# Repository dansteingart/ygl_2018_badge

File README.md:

## Overview

This is the sensor and code layout for the YGL 2018 Badge. 

The badge measures
- Ambient Temperature (via a DHT22 and a MLX90614)
- Focussed Temperature (via a MLX90614)
- Ambient Humidity (via a DHT22)

The badge also allows the wearer to indicate comfort level
- Red (hot)
- Blue (cold)
- Green (comfortable)

The badge attempts to connect to preprogammed wifi SSID's, and if it is connect it reports the ambient conditions once a minute and the user comfort on signaling.

## Board Schematics

The board can be edited in [Eagle](https://www.autodesk.com/products/eagle/free-download) 

## Code

The code for this is meant to be uploaded through the [build.particle.io](https://build.particle.io), but can also be compiled and sent remotely.

## How To Measure Things
This [document](https://docs.google.com/document/d/e/2PACX-1vTs8eymRHai5XaTd2wvhhjKwmNey0X5QBFbXBKoaI53rYneKwUvtwl-gOKRnENuz1WqiknrLIXWhSsD/pub)([PDF](https://docs.google.com/document/d/11KgSaUlBZMfQc9rQ66gh0Wr3Of6fnvB99Y8Q6VOIqZM/export?format=pdf)) describes how and why this all works, and what we're trying to do.

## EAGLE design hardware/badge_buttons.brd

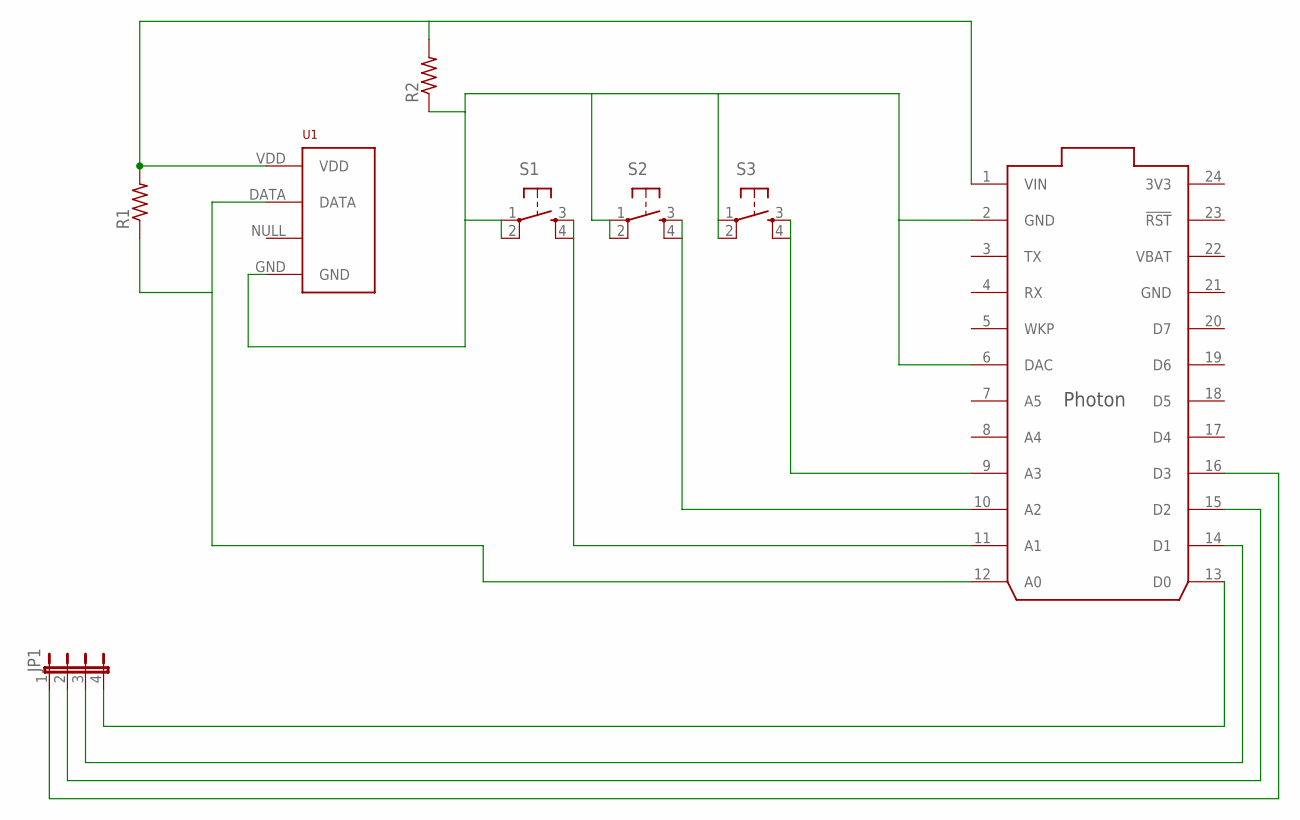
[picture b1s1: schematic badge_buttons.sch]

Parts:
JP1: JP4E; JP4
R1, R2: R-US_0204/7; 0204/7
S1, S2, S3: TAC_SWITCHPTH; TACTILE-PTH
U1: RHT03_DHT-22_AM2302; RHT03_DHT-22
U$1: PHOTON_WITH_HEADERS; PHOTON

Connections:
3V3: U$1.24 (3V3)
GND: U$1.21 (GND)
unnamed: S3.3, S3.4, U$1.9 (A3)
unnamed: S2.3, S2.4, U$1.10 (A2)
unnamed: S1.3, S1.4, U$1.11 (A1)
unnamed: R2.1, S1.1, S1.2, S2.1, S2.2, S3.1, S3.2, U1.GND, U$1.2 (GND), U$1.6 (DAC)
unnamed: R1.2, R2.2, U1.VDD, U$1.1 (VIN)
unnamed: R1.1, U1.DATA, U$1.12 (A0)
unnamed: JP1.4, U$1.13 (D0)
unnamed: JP1.3, U$1.14 (D1)
unnamed: JP1.2, U$1.15 (D2)
unnamed: JP1.1, U$1.16 (D3)
VBAT: U$1.22 (VBAT)

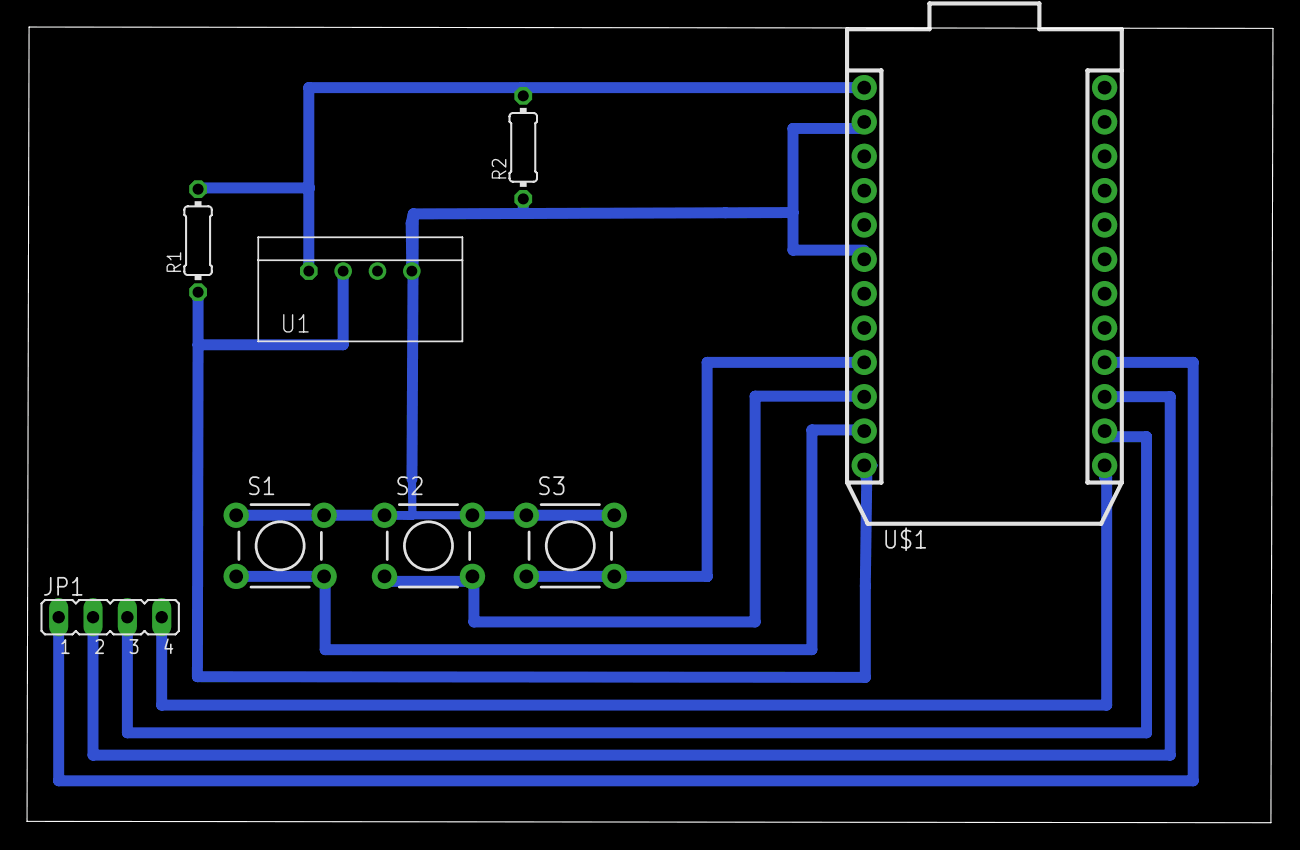
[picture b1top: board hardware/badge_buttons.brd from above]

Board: 2 copper layers, 92.2 x 58.9 mm, 8 parts (0 on the bottom side), 10 nets.

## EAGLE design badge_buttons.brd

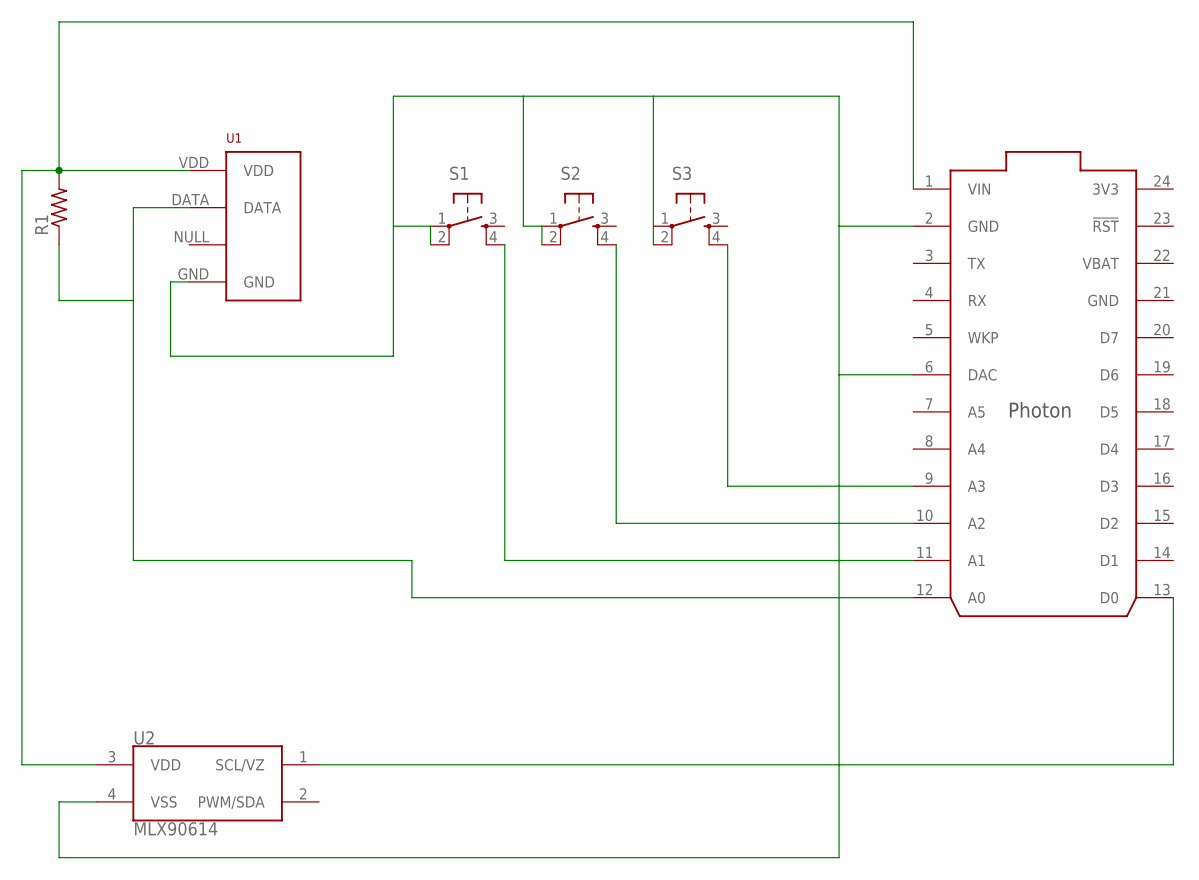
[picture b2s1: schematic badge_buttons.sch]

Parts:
R1: R-US_0204/7; 0204/7
S1, S2, S3: TAC_SWITCHPTH; TACTILE-PTH
U1: RHT03_DHT-22_AM2302; RHT03_DHT-22
U2: MLX90614; TO-39
U$1: PHOTON_WITH_HEADERS; PHOTON

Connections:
3V3: U$1.24 (3V3)
GND: U$1.21 (GND)
unnamed: S3.4, U$1.9 (A3)
unnamed: S2.4, U$1.10 (A2)
unnamed: S1.4, U$1.11 (A1)
unnamed: S1.1, S1.2, S2.1, S2.2, S3.1, S3.2, U1.GND, U2.4 (VSS), U$1.2 (GND), U$1.6 (DAC)
unnamed: R1.2, U1.VDD, U2.3 (VDD), U$1.1 (VIN)
unnamed: R1.1, U1.DATA, U$1.12 (A0)
unnamed: U2.1 (SCL/VZ), U$1.13 (D0)
VBAT: U$1.22 (VBAT)

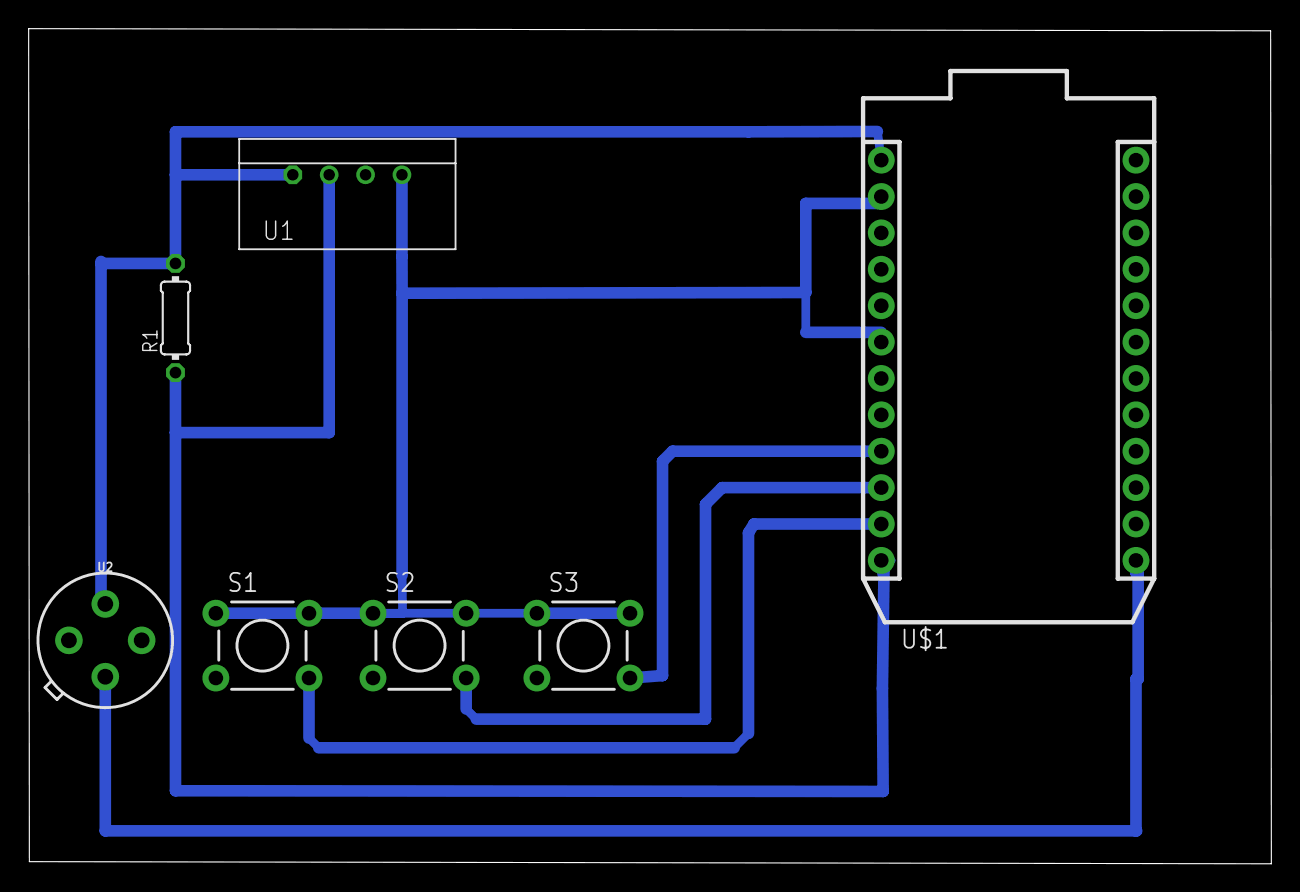
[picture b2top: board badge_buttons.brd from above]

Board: 2 copper layers, 86.8 x 58.3 mm, 7 parts (0 on the bottom side), 7 nets.

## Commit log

2018-05-30 first files
2018-06-07 clean up lines, add sensor loop
2018-06-07 fatten traces
2018-06-07 added README
2018-06-07 Rename README to README.md
2018-06-07 MLX succesfully added to code
2018-06-07 refactor directory/finish wiring
2018-06-07 started ToO
2018-06-07 more ToO
2018-06-08 add powershield SOC/Cell Potential
2018-06-08 fixed analogread bug
2018-06-08 code cleanup
2018-06-08 commented the ino
2018-06-08 Too much ToO
2018-06-08 sensible button order
2018-06-28 last add
2018-06-28 pusher T
2018-06-28 Wingoneer Change
2018-06-28 fattened pads
2018-06-28 othermill layout for 1x2 cut
2018-06-29 power hogging
2018-07-13 improve speed, triggers
2018-07-15 fix comfort send
2018-10-12 cleanup

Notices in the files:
parts and their libraries:
SparkFun-Retired: Licensing: Creative Commons ShareAlike 4.0 International - https://creativecommons.org/licenses/by-sa/4.0
Particle-Devices: Licensing: Designed by Particle.
